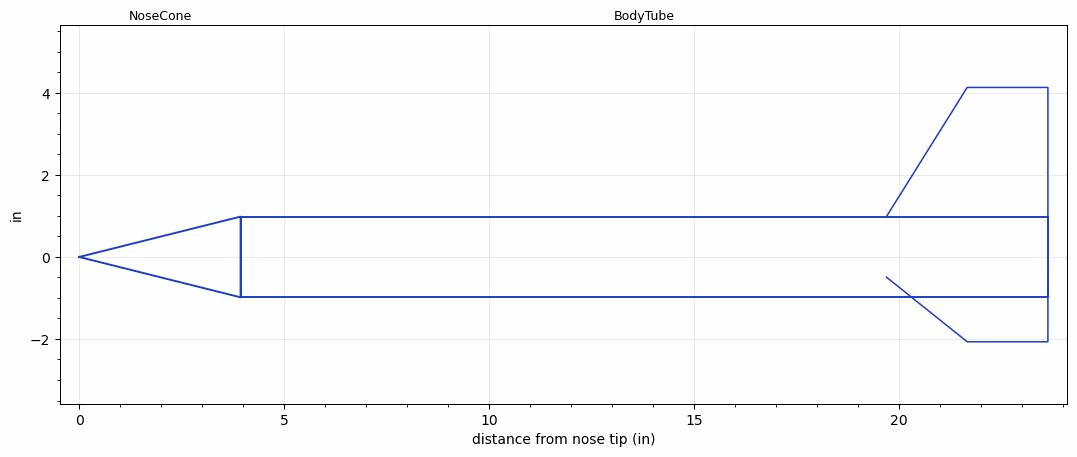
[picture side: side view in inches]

<RASAeroDocument>
 <FileVersion>2</FileVersion>
 <RocketDesign>
  <NoseCone>
   <Length>3.9370079</Length>
   <Diameter>1.9685039</Diameter>
   <Shape>Conical</Shape>
   <Location>0</Location>
  </NoseCone>
  <BodyTube>
   <Length>19.685039</Length>
   <Diameter>1.9685039</Diameter>
   <LaunchLugDiameter>0.23622047</LaunchLugDiameter>
   <LaunchLugLength>1.9685039</LaunchLugLength>
   <Location>3.9370079</Location>
   <Fin>
    <Count>3</Count>
    <Chord>3.9370079</Chord>
    <Span>3.1496063</Span>
    <SweepDistance>1.9685039</SweepDistance>
    <TipChord>1.9685039</TipChord>
    <Thickness>0.11811024</Thickness>
    <Location>3.9370079</Location>
    <AirfoilSection>Square</AirfoilSection>
   </Fin>
  </BodyTube>
  <Surface>Rough Camouflage Paint</Surface>
  <ModifiedBarrowman>False</ModifiedBarrowman>
  <Turbulence>False</Turbulence>
  <UseBooster1>False</UseBooster1>
  <UseBooster2>False</UseBooster2>
  <Comments>Exported by lo-fi-rocket from "r1-three-fin-conical".</Comments>
 </RocketDesign>
 <LaunchSite>
  <Altitude>0</Altitude>
  <Pressure>0</Pressure>
  <RodAngle>0</RodAngle>
  <RodLength>4.9212598</RodLength>
  <Temperature>59</Temperature>
  <WindSpeed>0</WindSpeed>
 </LaunchSite>
 <Recovery>
  <Altitude1>1000</Altitude1>
  <Altitude2>1000</Altitude2>
  <DeviceType1>Parachute</DeviceType1>
  <DeviceType2>None</DeviceType2>
  <Event1>True</Event1>
  <Event2>False</Event2>
  <Size1>11.811024</Size1>
  <Size2>0</Size2>
  <EventType1>Apogee</EventType1>
  <EventType2>None</EventType2>
  <CD1>0.8</CD1>
  <CD2>1.33</CD2>
 </Recovery>
 <SimulationList>
  <Simulation>
   <SustainerEngine>LF-D12  (LoFi)</SustainerEngine>
   <SustainerLaunchWt>0.42087103</SustainerLaunchWt>
   <SustainerCG>15.237088</SustainerCG>
   <SustainerIgnitionDelay>0</SustainerIgnitionDelay>
   <Booster1SeparationDelay>0</Booster1SeparationDelay>
   <Booster1IgnitionDelay>0</Booster1IgnitionDelay>
   <IncludeBooster1>False</IncludeBooster1>
   <Booster2Delay>0</Booster2Delay>
   <IncludeBooster2>False</IncludeBooster2>
  </Simulation>
 </SimulationList>
</RASAeroDocument>
